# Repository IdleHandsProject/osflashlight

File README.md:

# osflashlight
A beginner open source flashlight soldering kit.

Check out the video to build your own!

Instructables - https://www.instructables.com/id/Open-Source-Flashlight-Kit/

Thingiverse Files - https://www.thingiverse.com/thing:2841747

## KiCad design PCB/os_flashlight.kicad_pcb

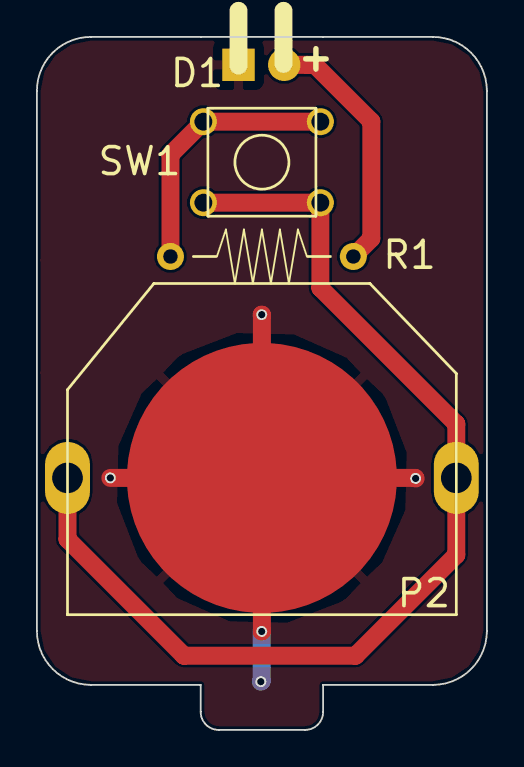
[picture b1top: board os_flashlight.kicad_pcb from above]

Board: 2 copper layers, 25.0 x 38.5 mm, 4 parts (0 on the bottom side), 4 nets.

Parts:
D1: LED; LED-10MM_RA
P2: BATT; CoinCellHolder_TH
R1: 100; Resistor_Horizontal_RM10mm_025W
SW1: SW_PUSH; SW_PUSH_SMALL_13mmHEIGHT

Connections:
GND: D1.1, P2.1
unnamed: D1.2, R1.2
unnamed: R1.1, SW1.2
VBATT: P2.2, SW1.1

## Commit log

2018-03-27 fixed PDF
2018-03-27 added links
